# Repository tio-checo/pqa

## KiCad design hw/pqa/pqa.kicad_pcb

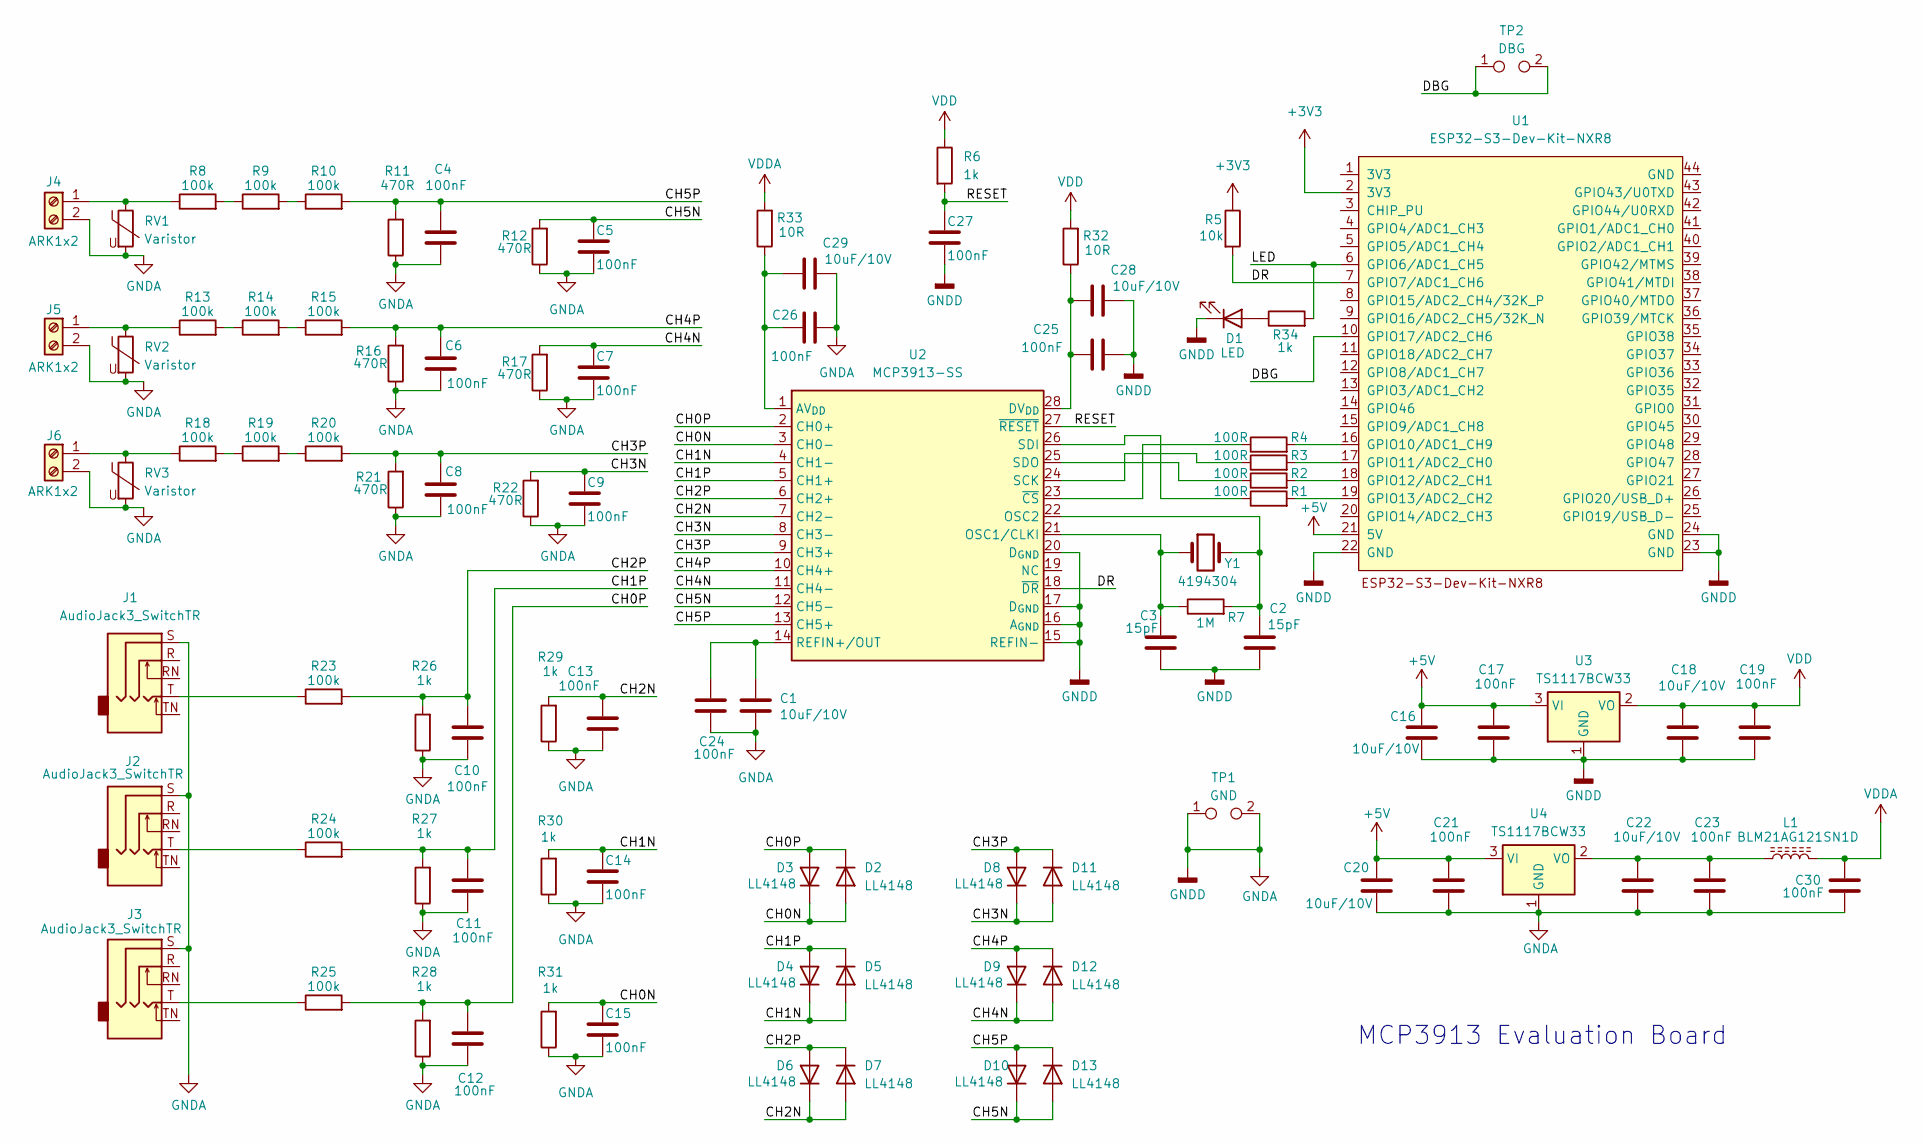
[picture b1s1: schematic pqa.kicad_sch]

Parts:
C1, C16, C18, C20, C22, C28, C29: 10uF/10V; C_0805_2012Metric_Pad1.18x1.45mm_HandSolder
C2, C3: 15pF; C_0805_2012Metric_Pad1.18x1.45mm_HandSolder
C4, C5, C6, C7, C8, C9, C10, C11, C12, C13, C14, C15, C17, C19, C21, C23, C24, C25, C26, C27, C30: 100nF; C_0805_2012Metric_Pad1.18x1.45mm_HandSolder
D1: LED; LED_D3.0mm
D2, D3, D4, D5, D6, D7, D8, D9, D10, D11, D12, D13: LL4148; D_MiniMELF
J1, J2, J3: AudioJack3_SwitchTR; Jack_3.5mm_ST214-C_Horizontal
J4, J5, J6: ARK1x2; TerminalBlock_Phoenix_PT-1,5-2-5.0-H_1x02_P5.00mm_Horizontal
L1: BLM21AG121SN1D; L_0805_2012Metric_Pad1.15x1.40mm_HandSolder
R1, R2, R3, R4: 100R; R_0805_2012Metric_Pad1.20x1.40mm_HandSolder
R5: 10k; R_0805_2012Metric_Pad1.20x1.40mm_HandSolder
R6, R26, R27, R28, R29, R30, R31, R34: 1k; R_0805_2012Metric_Pad1.20x1.40mm_HandSolder
R7: 1M; R_0805_2012Metric_Pad1.20x1.40mm_HandSolder
R8, R9, R10, R13, R14, R15, R18, R19, R20: 100k; R_1206_3216Metric_Pad1.30x1.75mm_HandSolder
R11, R12, R16, R17, R21, R22: 470R; R_0805_2012Metric_Pad1.20x1.40mm_HandSolder
R23, R24, R25: 100k; R_0805_2012Metric_Pad1.20x1.40mm_HandSolder
R32, R33: 10R; R_0805_2012Metric_Pad1.20x1.40mm_HandSolder
RV1, RV2, RV3: Varistor; RV_Disc_D9mm_W3.5mm_P5mm
TP1: GND; PinHeader_1x02_P2.54mm_Vertical
TP2: DBG; PinHeader_1x02_P2.54mm_Vertical
U1: ESP32-S3-Dev-Kit-NXR8
U2: MCP3913-SS; SSOP-28_5.3x10.2mm_P0.65mm_12mil
U3, U4: TS1117BCW33; SOT-223-3_TabPin2
Y1: 4194304; Crystal_HC49-U_Vertical

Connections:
+3V3: R5.1, U1.2 (3V3)
+5V: C16.1, C17.1, C20.1, C21.1, U1.21 (5V), U3.3 (VI), U4.3 (VI)
/CH0N: C15.1, D2.2 (A), D3.1 (K), R31.2, U2.3 (CH0-)
/CH0P: C12.1, D2.1 (K), D3.2 (A), R25.2, R28.2, U2.2 (CH0+)
/CH1N: C14.1, D4.1 (K), D5.2 (A), R30.2, U2.4 (CH1-)
/CH1P: C11.1, D4.2 (A), D5.1 (K), R24.2, R27.2, U2.5 (CH1+)
/CH2N: C13.1, D6.1 (K), D7.2 (A), R29.2, U2.7 (CH2-)
/CH2P: C10.1, D6.2 (A), D7.1 (K), R23.2, R26.2, U2.6 (CH2+)
/CH3N: C9.1, D8.1 (K), D11.2 (A), R22.2, U2.8 (CH3-)
/CH3P: C8.1, D8.2 (A), D11.1 (K), R20.2, R21.2, U2.9 (CH3+)
/CH4N: C7.1, D9.1 (K), D12.2 (A), R17.2, U2.11 (CH4-)
/CH4P: C6.1, D9.2 (A), D12.1 (K), R15.2, R16.2, U2.10 (CH4+)
/CH5N: C5.1, D10.1 (K), D13.2 (A), R12.2, U2.12 (CH5-)
/CH5P: C4.1, D10.2 (A), D13.1 (K), R10.2, R11.2, U2.13 (CH5+)
/DBG: TP2.1, TP2.2, U1.10 (GPIO17/ADC2_CH6)
/DR: R5.2, U1.7 (GPIO7/ADC1_CH6), U2.18 (~DR)
/LED: R34.2, U1.6 (GPIO6/ADC1_CH5)
/RESET: C27.1, R6.2, U2.27 (~RESET)
GNDA: C1.2, C2.2, C3.2, C4.2, C5.2, C6.2, C7.2, C8.2, C9.2, C10.2, C11.2, C12.2, C13.2, C14.2, C15.2, C16.2, C17.2, C18.2, C19.2, C20.2, C21.2, C22.2, C23.2, C24.2, C25.2, C26.2, C27.2, C28.2, C29.2, C30.2, D1.1 (K), J1.S, J2.S, J3.S, J4.2, J5.2, J6.2, R11.1, R12.1, R16.1, R17.1, R21.1, R22.1, R26.1, R27.1, R28.1, R29.1, R30.1, R31.1, RV1.2, RV2.2, RV3.2, TP1.1, TP1.2, U1.22 (GND), U1.23 (GND), U1.24 (GND), U2.15 (REFIN-), U2.16 (A_{GND}), U2.17 (D_{GND}), U2.20 (D_{GND}), U3.1 (GND), U4.1 (GND)
unnamed: D1.2 (A), R34.1
unnamed: J1.T, R23.1
unnamed: J2.T, R24.1
unnamed: J3.T, R25.1
unnamed: J4.1, R8.1, RV1.1
unnamed: J5.1, R13.1, RV2.1
unnamed: J6.1, R18.1, RV3.1
unnamed: R8.2, R9.1
unnamed: R9.2, R10.1
unnamed: R13.2, R14.1
unnamed: R14.2, R15.1
unnamed: R18.2, R19.1
unnamed: R19.2, R20.1
unnamed: R4.2, U1.16 (GPIO10/ADC1_CH9)
unnamed: R3.2, U1.17 (GPIO11/ADC2_CH0)
unnamed: R2.2, U1.18 (GPIO12/ADC2_CH1)
unnamed: R1.2, U1.19 (GPIO13/ADC2_CH2)
unnamed: C26.1, C29.1, R33.1, U2.1 (AV_{DD})
unnamed: C25.1, C28.1, R32.1, U2.28 (DV_{DD})
unnamed: C3.1, R7.1, U2.21 (OSC1/CLKI), Y1.1
unnamed: C2.1, R7.2, U2.22 (OSC2), Y1.2
unnamed: C1.1, C24.1, U2.14 (REFIN+/OUT)
unnamed: R3.1, U2.24 (SCK)
unnamed: R1.1, U2.26 (SDI)
unnamed: R2.1, U2.25 (SDO)
unnamed: R4.1, U2.23 (~CS)
unnamed: C22.1, C23.1, L1.1, U4.2 (VO)
VDD: C18.1, C19.1, R6.1, R32.2, U3.2 (VO)
VDDA: C30.1, L1.2, R33.2

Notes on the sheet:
MCP3913 Evaluation Board

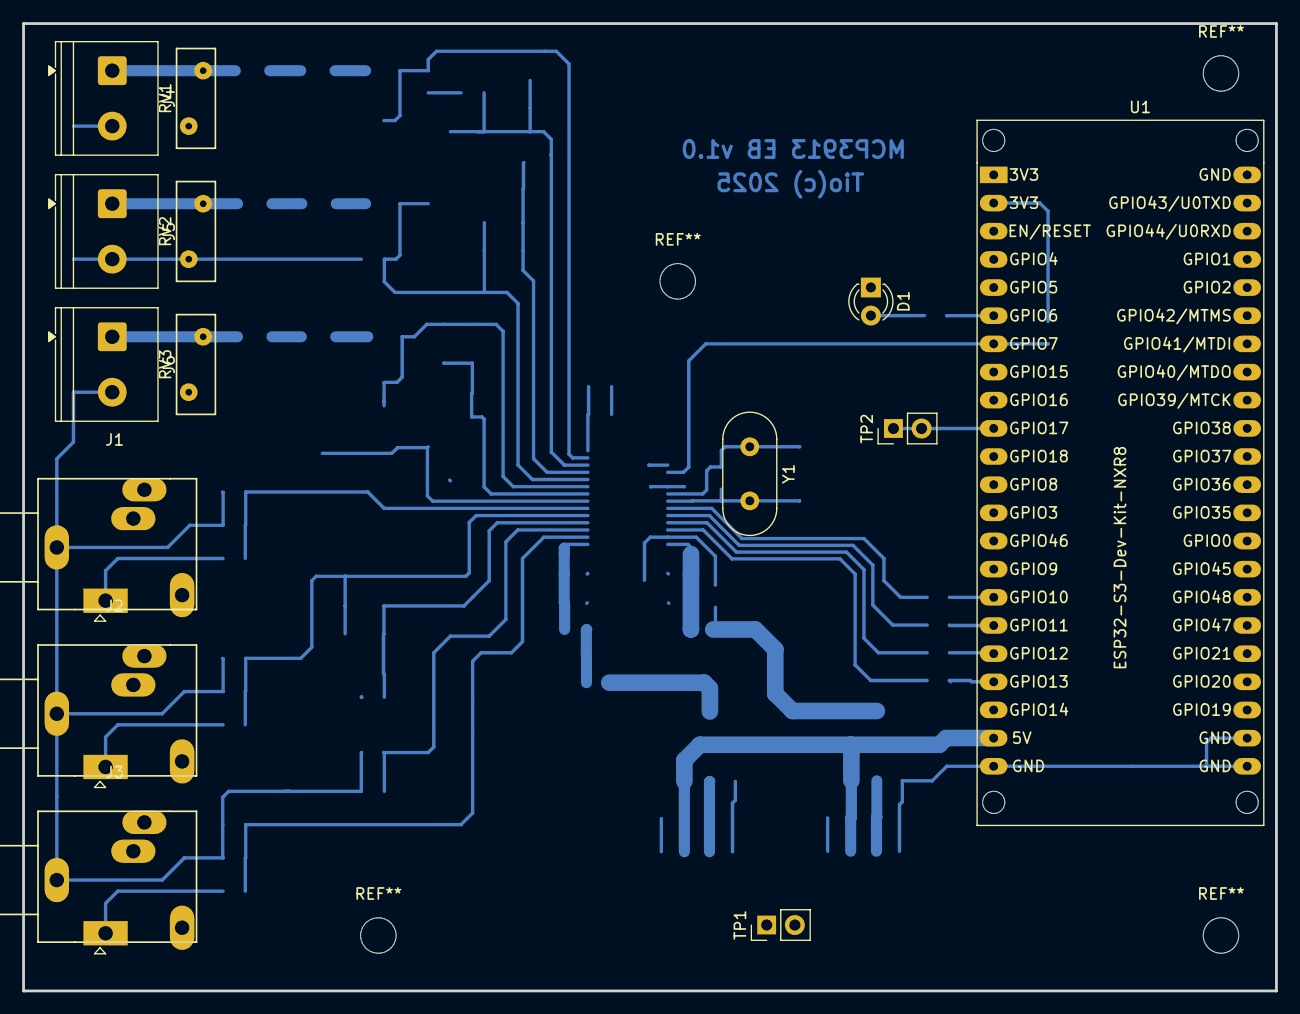
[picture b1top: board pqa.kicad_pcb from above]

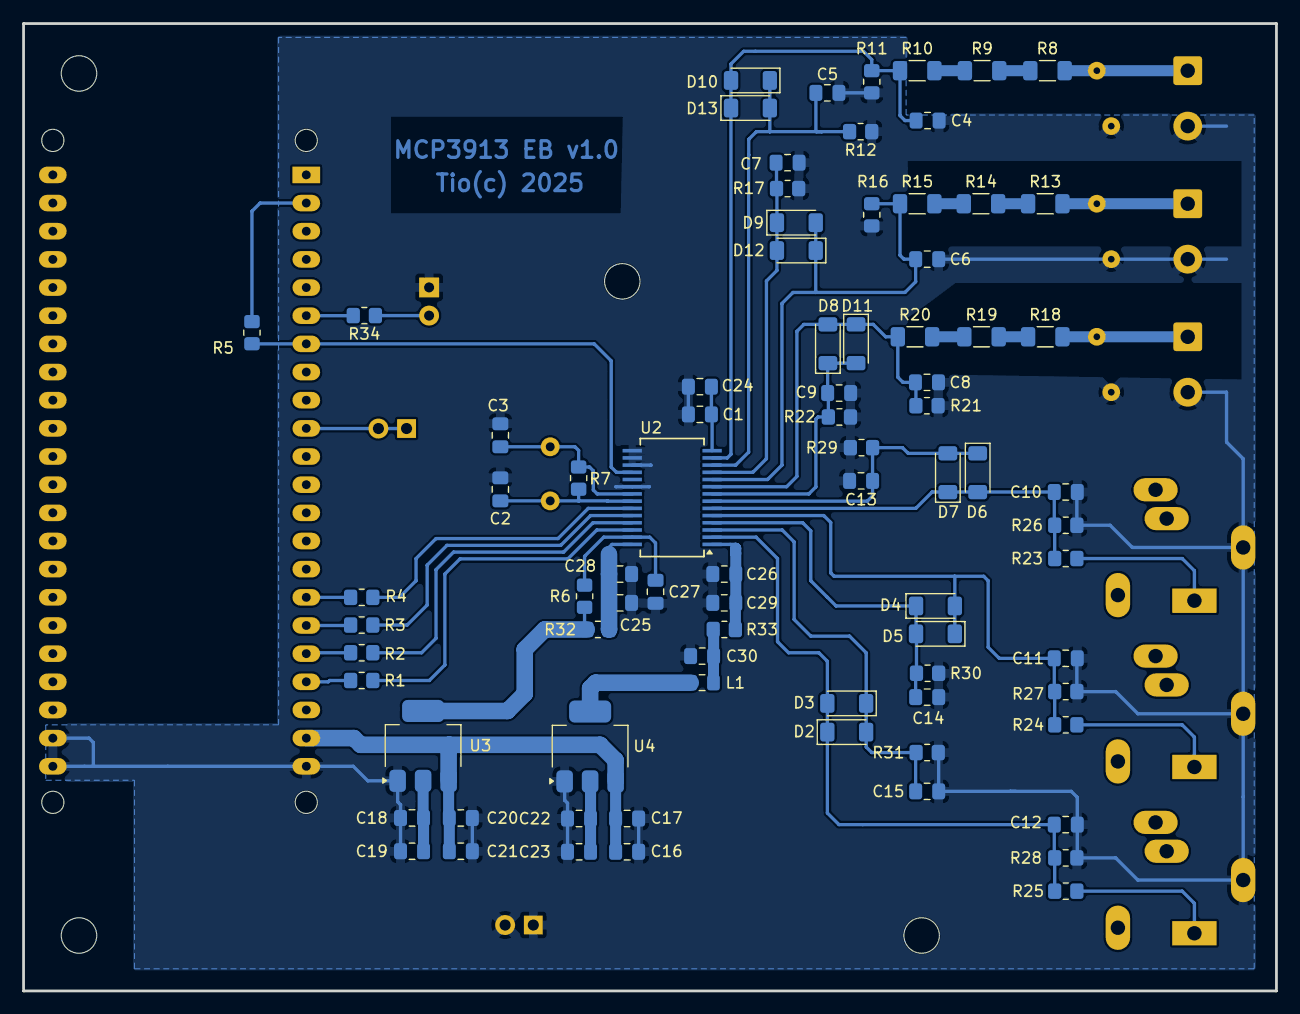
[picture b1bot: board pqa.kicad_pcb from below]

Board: 2 copper layers, 113.0 x 87.2 mm, 94 parts (80 on the bottom side), 48 nets.

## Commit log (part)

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2025-12-10 pqa fw - Initial commit
    Initial commit of pqa fw for ESP32-S3 platform.
2025-12-16 pqa fw - Measure grid frequency on channel DAQ_CHANNEL_U3
2025-12-29 pqa fw - Add timestamp to calculated values and JSON
2025-12-29 Let Git ignore .DS_Store MacOS system file
2025-12-29 pqa fw - Send total active power to Thingspeak and in JSON
2026-04-24 pqa fw - Do not expose credentials
2026-04-27 pqa hw - KiCad schema and pcb
    KiCad schema and pcb
2026-04-28 pqa matlab - Matlab m-files
    Matlab m-files

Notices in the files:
hw/pqa/pqa.kicad_pcb:
Tio(c) 2025
